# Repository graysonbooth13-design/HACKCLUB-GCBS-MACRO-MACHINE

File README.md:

[HACK.CLUB.MACRO.BOM.csv](https://github.com/user-attachments/files/24020276/HACK.CLUB.MACRO.BOM.csv)# HACKCLUB-GCBS-MACRO-MACHINE
This is my first GitHub repo so it is a work in progress but I built this macro pad for the hackclub project
If you have any ideas or concerns I am fully open to critisism just leave a comment! :)

GRAYSONS MACRO MACHINE
GRAYSONS MACRO MACHINE is a 5 key macropad. It also has 4 SK6812 MINI-E LEDs, and uses QMK firmware

Features:
2 peice 3d printed case. Custom colors ooooohhh.
4 SK6812 MINI-E RGB LEDs. these should work as under glow for the keys.
5 Keys!
CADModel:

It has 2 seperate printed pieces. The base where the PCB sits, and the top cover.

Schematic:

Made in KiCAd.

PCB:

3d file of the PCB (With components =>)

Here's my PCB! It was made in KiCad.

Firmware Overview
This hackpad uses QMK firmware for everything.

I might add more in the future! That's it for now

BOM:

1;"D1,D4,D3,D2";"LED_SK6812MINI_PLCC4_3.5x3.5mm_P1.75mm";4;"SK6812MINI";;;
2;"SW1,SW3,SW5,SW2,SW4";"SW_Cherry_MX_1.00u_PCB";5;"SW_Push";;;
3;"U1";"XIAO-RP2040-DIP";1;"XIAO-RP2040-DIP";;;

(Above is the CSV version of the BOM and below is just normal)

Here should be everything you need to make this hackpad

5x Cherry MX Blue Switches

5x DSA Keycaps

4x M3x5x4 Heatset inserts

4x M3x16mm SHCS Bolts

4x SK6812 MINI-E LED

1x XIAO RP2040

1x Case (2 printed parts)

JOKE TIMMEEEEEE
What happenes when you eat tinfoil

you...sheet metal :)

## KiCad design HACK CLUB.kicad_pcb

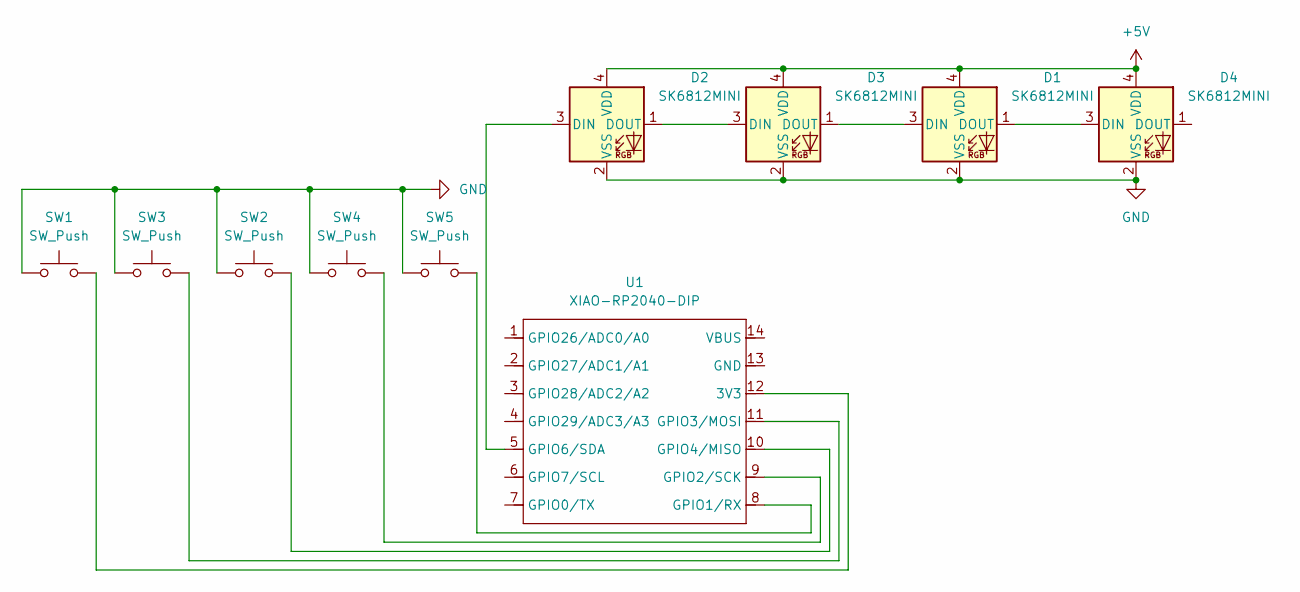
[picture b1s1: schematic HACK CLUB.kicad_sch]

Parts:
D1, D2, D3, D4: SK6812MINI; LED_SK6812MINI_PLCC4_3.5x3.5mm_P1.75mm
SW1, SW2, SW3, SW4, SW5: SW_Push; SW_Cherry_MX_1.00u_PCB
U1: XIAO-RP2040-DIP

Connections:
+5V: D1.4 (VDD), D2.4 (VDD), D3.4 (VDD), D4.4 (VDD)
GND: D1.2 (VSS), D2.2 (VSS), D3.2 (VSS), D4.2 (VSS), SW1.1, SW2.1, SW3.1, SW4.1, SW5.1
unnamed: D1.3 (DIN), D3.1 (DOUT)
unnamed: D1.1 (DOUT), D4.3 (DIN)
unnamed: D2.3 (DIN), U1.5 (GPIO6/SDA)
unnamed: D2.1 (DOUT), D3.3 (DIN)
unnamed: SW1.2, U1.12 (3V3)
unnamed: SW5.2, U1.8 (GPIO1/RX)
unnamed: SW4.2, U1.9 (GPIO2/SCK)
unnamed: SW3.2, U1.11 (GPIO3/MOSI)
unnamed: SW2.2, U1.10 (GPIO4/MISO)

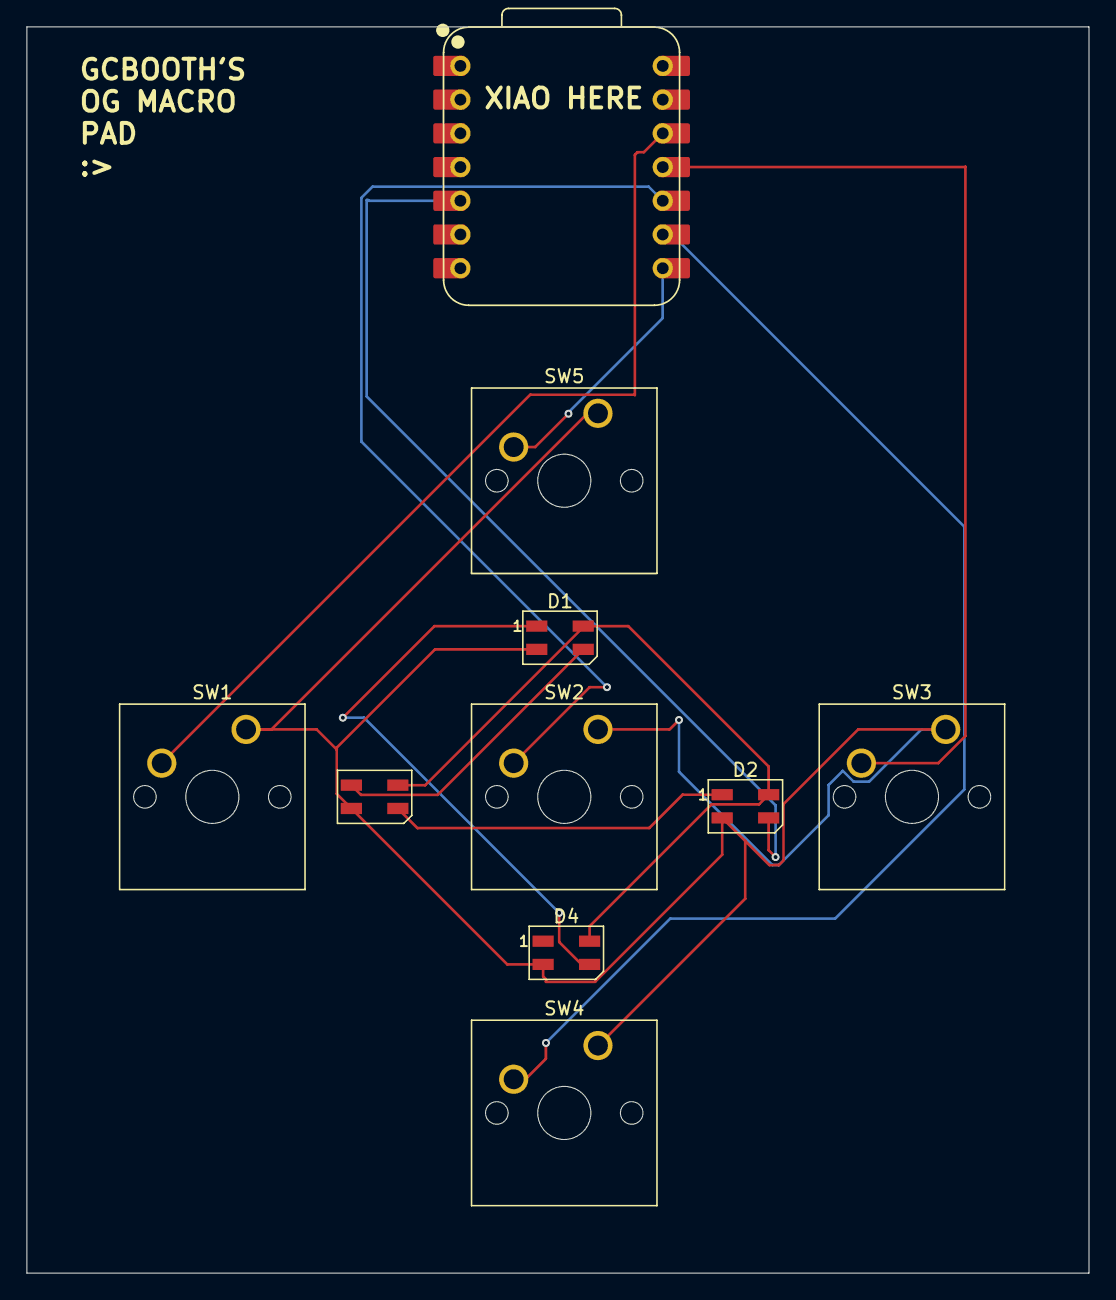
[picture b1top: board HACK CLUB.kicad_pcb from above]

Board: 2 copper layers, 80.0 x 93.9 mm, 10 parts (0 on the bottom side), 11 nets.

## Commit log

2025-12-05 Invite feedback on the macro pad project
    Added a note inviting feedback and suggestions.
2025-12-05 CASE BOTTOM PART
2025-12-05 Macro machine case top part
    Top part of case
2025-12-05 Create cad
2025-12-06 Enhance README with project details and images
    Expanded README with detailed project features, schematics, and BOM.
2025-12-06 3d STEP FILES
2025-12-06 Create 3D STEP FILES+ 3D FILE PHOTOS
2025-12-06 PCB+ ECT/
2025-12-06 Create PCB + ECT
2025-12-06 PCB AND MORE
2025-12-06 Add PCB files directory
    This commit adds a new file for PCB designs.
2025-12-06 Create s
2025-12-06 Fix formatting and punctuation in README features
    Updated feature list with improved formatting.
2025-12-06 Create MACRO CODE
2025-12-13 Top and bottom case step file
2025-12-13 TOP+BOTTOM PHOTO
2025-12-13 Replace images with updated CAD model
    Updated images in README with new CAD model.
2025-12-14 Fix typo in README regarding BOM version
2025-12-15 Revise README for clarity and grammar
    Updated text for clarity and corrected typos.
